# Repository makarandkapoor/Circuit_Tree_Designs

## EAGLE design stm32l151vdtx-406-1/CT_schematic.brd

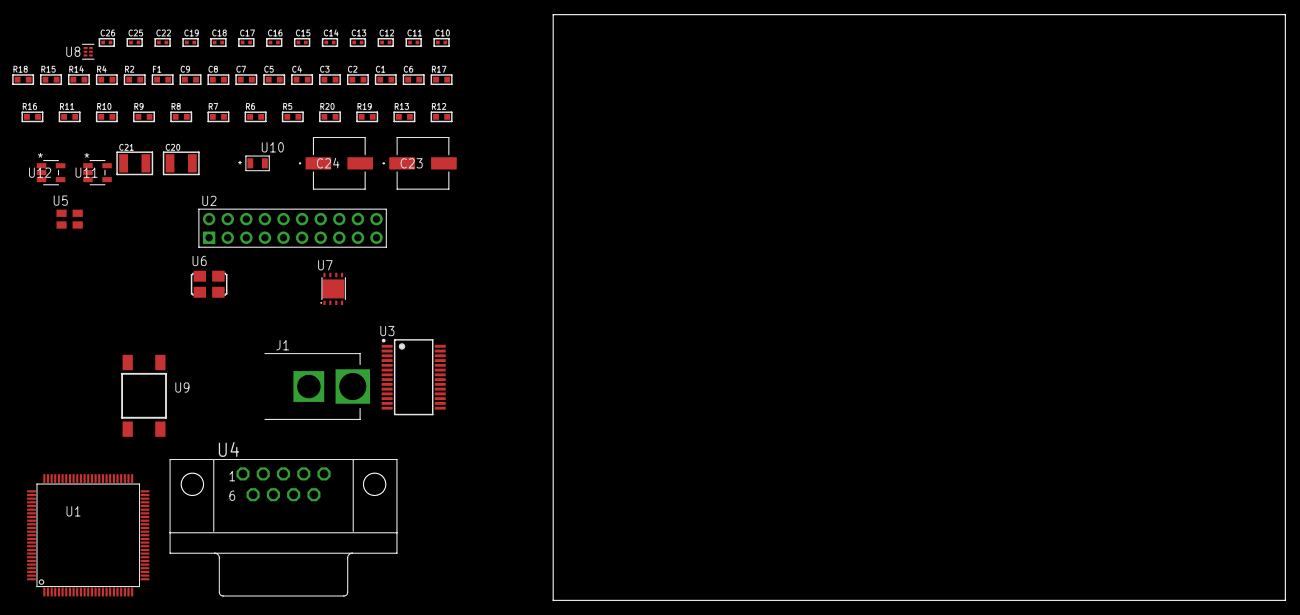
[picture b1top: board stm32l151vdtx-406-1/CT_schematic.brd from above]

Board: 2 copper layers, 100.0 x 80.0 mm, 58 parts (0 on the bottom side), 37 nets, no tracks yet.

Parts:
C1, C2, C3, C4, C5, C7: 1e-07; C0603
C6: 4.7e-06; C0603
C8: 1e-08; C0603
C9: 1e-06; C0603
C10, C11, C12, C13, C14, C15, C16, C22: 1e-07; C0402
C17, C18, C19, C25, C26: 1e-08; C0402
C20, C21: 1e-05; C1210
C23, C24: 0.0001; EXV-9H
F1: 240.0; L0603
J1: PJ-037B; PJ-037B_PACKAGE
R2, R15: 1000.0; R0603
R4: 4700.0; R0603
R5, R6, R7, R8, R9, R10, R11, R16, R17: 10000.0; R0603
R12, R13: 100000.0; R0603
R14: 2231.0; R0603
R18: 9100.0; R0603
R19: 680000.0; R0603
R20: 120000.0; R0603
U1: STM32L151VDT6; LQFP100
U2: TST-110-05-T-D-RA
U3: ST3241EBPR; SSOP-28
U4: 182-009-113R531; 182-009-MALE
U5: ASEK-32.768KHz-ECST; ASEK
U6: ASFL1-25MHZ-NCS; ASFL1
U7: LP3878SDX-ADJ/NOPB; WSON-8
U8: TPS3895ADRYR; SON-6
U9: 4-1437565-2; SW_4-1437565-2
U10: Q65110A2395; LGM67K-G1J2-24-Z
U11, U12: nc7sz125m5x; NC7SZ125M5X

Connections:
CLK_U1_8: U1.8, U5.3
CLK_U1_12: U1.12, U6.3
GND: C1.2, C2.2, C3.2, C4.2, C5.2, C6.2, C7.2, C8.2, C9.2, C10.2, C11.2, C12.2, C15.2, C16.2, C17.2, C18.2, C19.2, C20.2, C21.2, C22.2, C23.2, C24.2, C25.2, C26.2, J1.2, R2.2, R5.2, R11.2, R15.2, R18.2, R20.2, U1.10, U1.19, U1.20, U1.27, U1.49, U1.74, U1.99, U2.4, U2.6, U2.8, U2.10, U2.12, U2.14, U2.16, U2.18, U2.20, U3.23, U3.25, U4.5, U5.2, U6.2, U7.3, U7.PAD, U8.2, U10.C, U11.2, U11.3, U12.1, U12.3
NET_U1_6: C7.1, U1.6
NET_U1_14: R4.1, U1.14, U12.4
NET_U1_22: C8.1, C9.1, F1.1, U1.21, U1.22
NET_U1_94: R5.1, U1.94
NET_U1_98: U9.3, U9.4
NET_U2_19: R11.1, U2.19
NET_U3_1: C14.1, U3.1
NET_U3_2: C14.2, U3.2
NET_U3_3: C16.1, U3.3
NET_U3_22: R12.1, U3.22
NET_U3_24: C13.2, U3.24
NET_U3_27: C15.1, U3.27
NET_U3_28: C13.1, U3.28
NET_U4_2: U3.4, U4.2
NET_U4_3: U3.9, U4.3
NET_U4_7: U3.5, U4.7
NET_U4_8: U3.10, U4.8
NET_U7_1: C19.1, U7.1
NET_U7_6: R14.2, R15.1, U7.6
NET_U7_8: R13.1, U7.8
NET_U8_1: R17.1, R18.1, U8.1
NET_U8_3: R19.2, R20.1, U8.3
NET_U8_4: R16.1, U8.4, U11.4, U12.2
NET_U9_1: R2.1, U9.1, U9.2
PROC_SYS_JTCK_SWCLK: R9.1, U1.76, U2.9
PROC_SYS_JTDI: R7.1, U1.77, U2.5
PROC_SYS_JTDO_TRACESWO: U1.89, U2.13
PROC_SYS_JTMS_SWDIO: R8.1, U1.72, U2.7
PROC_SYS_JTRST: R6.1, U1.90, U2.3
PROC_UART4_RX: U1.79, U3.19
PROC_UART4_TX: U1.78, U3.14
RST_OUT_U2_SRESET_B: R10.1, U2.15, U11.1
VCC_S1_12V4: C20.1, C23.1, C24.1, J1.1, R13.2, U7.4
VCC_TIER1_3V3: C1.1, C2.1, C3.1, C4.1, C5.1, C6.1, C10.1, C11.1, C12.1, C17.1, C18.1, C21.1, C22.1, C25.1, C26.1, F1.2, R4.2, R6.2, R7.2, R8.2, R9.2, R10.2, R12.2, R14.1, R16.2, R17.2, R19.1, U1.11, U1.28, U1.50, U1.75, U1.100, U2.1, U2.2, U3.26, U5.4, U6.4, U7.5, U8.6, U11.5, U12.5

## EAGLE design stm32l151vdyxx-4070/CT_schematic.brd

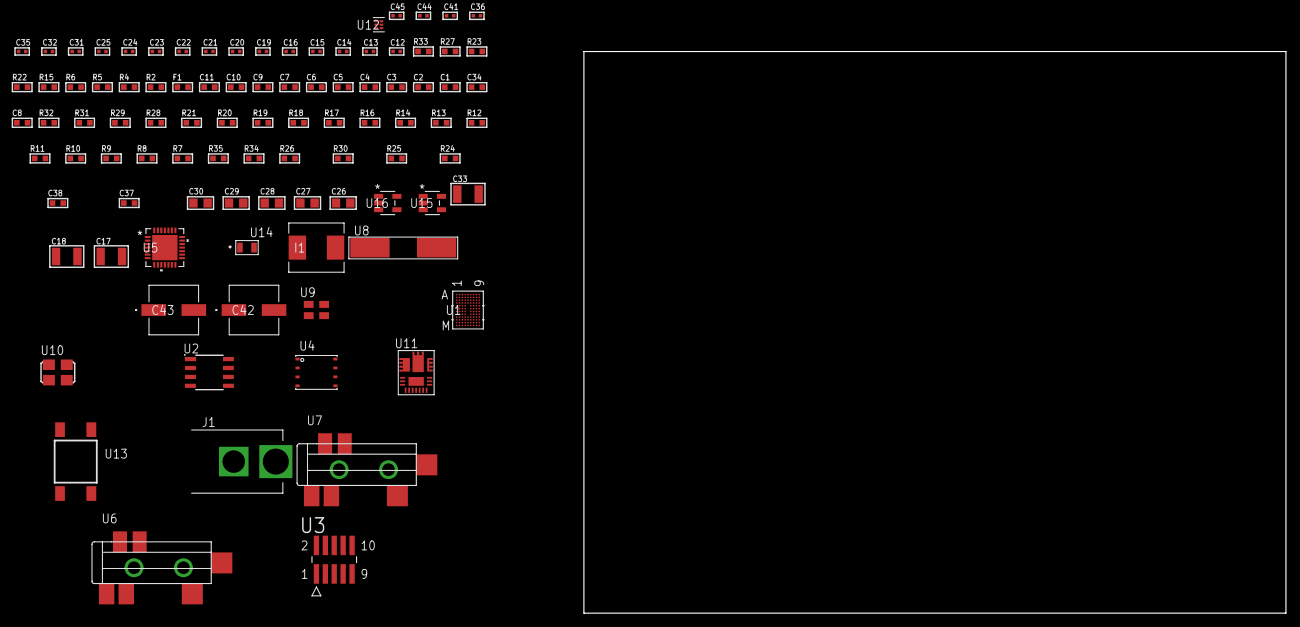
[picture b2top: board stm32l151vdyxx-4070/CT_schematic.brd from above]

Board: 2 copper layers, 100.0 x 80.0 mm, 95 parts (0 on the bottom side), 50 nets, no tracks yet.

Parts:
C1, C2, C3, C4, C5, C6, C7, C9: 1e-07; C0603
C8: 4.7e-06; C0603
C10: 1e-08; C0603
C11: 1e-06; C0603
C12, C13: 1e-11; C0402
C14, C16, C31, C32, C44, C45: 1e-08; C0402
C15, C21, C22, C23, C24, C25, C35, C36, C41: 1e-07; C0402
C17, C18: 2.2e-05; C1210
C19, C20: 1e-09; C0402
C26, C27, C28, C29, C30: 1e-05; C0805
C33: 0.0001; C1210
C34: 2.2e-06; C0603
C37: 8.7488758840791e-09; R0603
C38: 2.9825713241179e-07; R0603
C42, C43: 0.0001; EXV-9H
F1: 240.0; L0603
I1: 6.8e-07; IND25X25CZ
J1: PJ-037B; PJ-037B_PACKAGE
R2: 1000.0; R0603
R4: 4700.0; R0603
R5, R6: 2200.0; R0603
R7, R8, R9, R10, R11, R12, R13, R14, R16, R17, R18, R31, R32: 10000.0; R0603
R15: 5.0; R0603
R19, R20, R21: 47000.0; R0603
R22: 680.0; R0603
R23: 0.1; R0603
R24: 4030.2416170974; R0603
R25: 719.68600305311; R0603
R26: 58.26650887574; R0603
R27: 130.0; R0603
R28: 39000.0; R0603
R29: 49900.0; R0603
R30: 5113.9346405229; R0603
R33: 9100.0; R0603
R34: 680000.0; R0603
R35: 120000.0; R0603
U1: STM32L151VDY6XTR; WLCSP104
U2: AT25320B-SSHL-T; SOIC-8
U3: FTSH-105-01-L-DV-K; SAMTEC_FTSH-105-01-L-DV-K
U4: 24AA256-I/MF; DFN8-S
U5: WM8731CLSEFL; QFN-28
U6, U7: SJ-43515TS-SMT-TR
U8: ABLS-25.000MHZ-B2F-T
U9: ASEK-32.768KHz-ECST; ASEK
U10: ASFL1-12.288MHZ-EC-T; ASFL1
U11: IR3899MTR1PBF
U12: TPS3895ADRYR; SON-6
U13: 4-1437565-2; SW_4-1437565-2
U14: Q65110A2395; LGM67K-G1J2-24-Z
U15, U16: nc7sz125m5x; NC7SZ125M5X

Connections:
CLK_CRYSTAL_U1_F8: C12.1, U1.F8, U8.1
CLK_CRYSTAL_U1_F9: C13.1, U1.F9, U8.2
CLK_U1_D8: U1.D8, U9.3
CLK_U5_1: U5.1, U10.3
GND: C1.2, C2.2, C3.2, C4.2, C5.2, C6.2, C7.2, C8.2, C9.2, C10.2, C11.2, C12.2, C13.2, C14.2, C15.2, C16.2, C20.2, C21.2, C22.2, C23.2, C24.2, C25.2, C26.2, C27.2, C28.2, C29.2, C30.2, C31.2, C32.2, C34.2, C35.2, C36.2, C41.2, C42.2, C43.2, C44.2, C45.2, J1.2, R2.2, R7.2, R14.2, R15.2, R17.2, R18.2, R19.2, R20.2, R21.2, R23.1, R23.2, R25.2, R28.2, R30.2, R33.2, R35.2, U1.A1, U1.C7, U1.D2, U1.E8, U1.H8, U1.J9, U1.K8, U1.L2, U1.M1, U2.4, U3.3, U3.5, U4.4, U5.4, U5.15, U5.19, U5.25, U5.26, U5.29, U6.1, U7.1, U9.2, U10.2, U11.4, U11.11, U11.17, U12.2, U14.C, U15.2, U15.3, U16.1, U16.3
NET_U1_A7: R7.1, U1.A7
NET_U1_B6: R6.1, U1.B6, U4.5
NET_U1_C5: R5.1, U1.C5, U4.6
NET_U1_E7: C9.1, U1.E7
NET_U1_F7: R4.1, U1.F7, U16.4
NET_U1_G6: C10.1, C11.1, F1.1, U1.G6, U1.G7
NET_U1_M8: U13.3, U13.4
NET_U2_3: R8.1, U2.3
NET_U2_7: R10.1, U2.7
NET_U3_9: R15.1, U3.9
NET_U4_1: R16.1, U4.1
NET_U4_2: R17.1, U4.2
NET_U4_3: R18.1, U4.3
NET_U5_20: C25.1, C30.1, U5.20
NET_U6_2: C18.1, R20.1, U6.2
NET_U6_5: C17.1, R19.1, U6.5
NET_U7_5: C19.1, C20.1, R21.1, R22.1, U7.5
NET_U11_1: C37.1, R24.1, R25.1, R26.1, R27.1, U11.1, U11.8
NET_U11_2: C36.1, U11.2
NET_U11_3: C37.2, C38.1, C38.2, U11.3
NET_U11_5: R28.1, U11.5
NET_U11_10: C34.1, U11.10
NET_U11_12: C33.1, I1.1, U11.12
NET_U11_14: C33.2, U11.14
NET_U11_15: R29.1, R30.1, U11.15
NET_U11_ATNET_3: I1.2, R24.2
NET_U11_ATNET_4: C38.2, R26.2
NET_U12_1: R32.1, R33.1, U12.1
NET_U12_3: R34.2, R35.1, U12.3
NET_U12_4: R31.1, U12.4, U15.4, U16.2
NET_U13_1: R2.1, U13.1, U13.2
PROC_I2S2_CK: U1.D4, U5.7
PROC_I2S2_SD: U1.A3, U5.8
PROC_I2S2_WS: U1.A2, U5.9, U5.11
PROC_SPI1_MISO: U1.A5, U2.2
PROC_SPI1_MOSI: U1.A6, U2.5
PROC_SPI1_NSS: R9.1, U1.J7, U2.1
PROC_SPI1_SCK: U1.K5, U2.6
PROC_SYS_JTCK_SWCLK: R14.1, U1.D3, U3.4
PROC_SYS_JTDI: R12.1, U1.B1, U3.8
PROC_SYS_JTDO_TRACESWO: U1.B5, U3.6
PROC_SYS_JTMS_SWDIO: R13.1, U1.E3, U3.2
RST_OUT_U3_JTAG_RST_B: R11.1, U3.10, U15.1
VCC_S1_16V9: C35.1, C42.1, C43.1, J1.1, R29.2, U11.9
VCC_TIER1_3V3: C1.1, C2.1, C3.1, C4.1, C5.1, C6.1, C7.1, C8.1, C14.1, C15.1, C16.1, C21.1, C22.1, C23.1, C24.1, C26.1, C27.1, C28.1, C29.1, C31.1, C32.1, C41.1, C44.1, C45.1, F1.2, I1.2, R4.2, R5.2, R6.2, R8.2, R9.2, R10.2, R11.2, R12.2, R13.2, R16.2, R24.2, R31.2, R32.2, R34.1, U1.A9, U1.B8, U1.C1, U1.E9, U1.K3, U1.L8, U1.M9, U2.8, U3.1, U4.7, U4.8, U5.3, U5.5, U5.12, U5.18, U9.4, U10.4, U12.6, U15.5, U16.5

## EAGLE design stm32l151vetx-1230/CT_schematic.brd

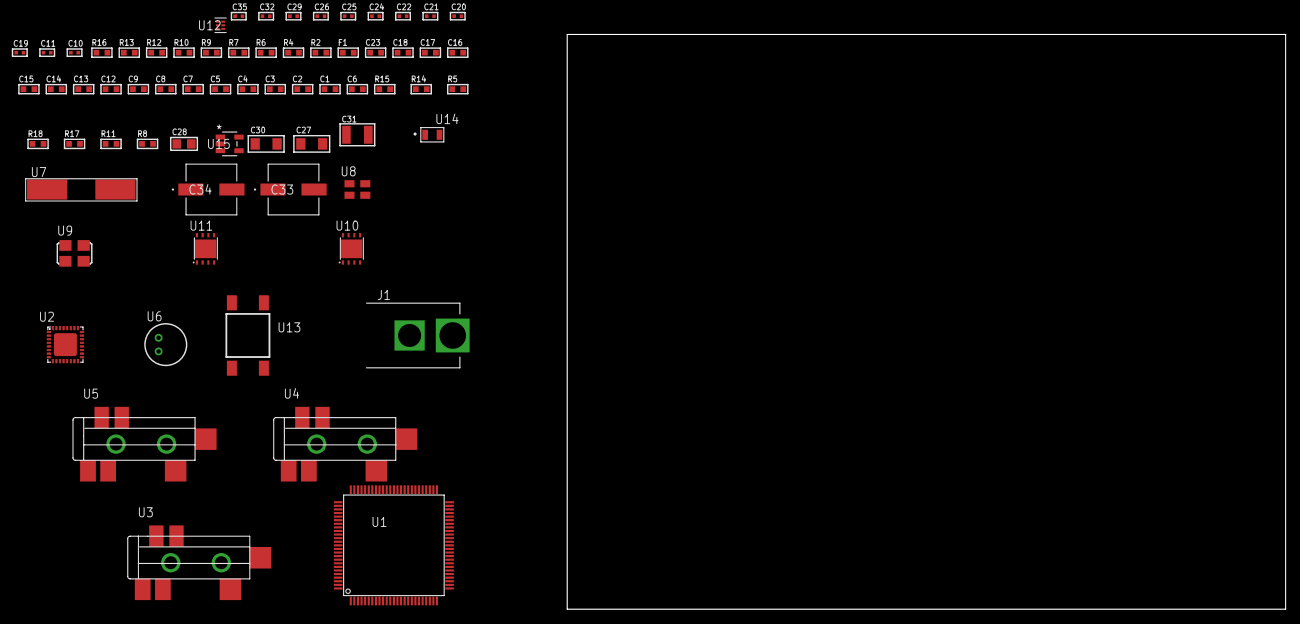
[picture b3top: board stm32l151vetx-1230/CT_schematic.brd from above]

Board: 2 copper layers, 100.0 x 80.0 mm, 68 parts (0 on the bottom side), 39 nets, no tracks yet.

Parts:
C1, C2, C3, C4, C5, C7: 1e-07; C0603
C6: 4.7e-06; C0603
C8: 1e-08; C0603
C9, C12, C13, C14, C15, C16, C17, C18, C23: 1e-06; C0603
C10, C11: 1e-11; C0402
C19, C20, C21, C22, C32: 1e-07; C0402
C24, C25, C26, C29, C35: 1e-08; C0402
C27, C30: 1e-05; C1206
C28: 1e-05; C0805
C31: 1e-05; C1210
C33, C34: 0.0001; EXV-9H
F1: 240.0; L0603
J1: PJ-037B; PJ-037B_PACKAGE
R2, R10, R13: 1000.0; R0603
R4: 4700.0; R0603
R5, R14, R15: 10000.0; R0603
R6, R7: 1270.0; R0603
R8, R11: 100000.0; R0603
R9: 200.0; R0603
R12: 2231.0; R0603
R16: 9100.0; R0603
R17: 680000.0; R0603
R18: 120000.0; R0603
U1: STM32L151VET7; LQFP100
U2: SGTL5000XNAA3; QFN-32
U3, U4, U5: SJ-43515TS-SMT-TR
U6: WM-64PCT; WM-64PC
U7: ABLS-25.000MHZ-B2F-T
U8: ASEK-32.768KHz-ECST; ASEK
U9: ASFL-24.57MHZ-NCS; ASFL1
U10, U11: LP3878SDX-ADJ/NOPB; WSON-8
U12: TPS3895ADRYR; SON-6
U13: 4-1437565-2; SW_4-1437565-2
U14: Q65110A2395; LGM67K-G1J2-24-Z
U15: nc7sz125m5x; NC7SZ125M5X

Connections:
CLK_CRYSTAL_U1_12: C10.1, U1.12, U7.1
CLK_CRYSTAL_U1_13: C11.1, U1.13, U7.2
CLK_U1_8: U1.8, U8.3
CLK_U2_21: U2.21, U9.3
GND: C1.2, C2.2, C3.2, C4.2, C5.2, C6.2, C7.2, C8.2, C9.2, C10.2, C11.2, C19.2, C20.2, C21.2, C22.2, C23.2, C24.2, C25.2, C26.2, C27.2, C28.2, C29.2, C30.2, C31.2, C32.2, C33.2, C34.2, C35.2, J1.2, R2.2, R5.2, R7.2, R10.2, R13.2, R16.2, R18.2, U1.10, U1.19, U1.20, U1.27, U1.49, U1.74, U1.99, U2.1, U2.3, U2.7, U2.EXP, U4.1, U5.1, U6.2, U8.2, U9.2, U10.3, U10.PAD, U11.3, U11.PAD, U12.2, U14.C, U15.1, U15.3
NET_U1_6: C7.1, U1.6
NET_U1_14: R4.1, U1.14, U15.4
NET_U1_22: C8.1, C9.1, F1.1, U1.21, U1.22
NET_U1_94: R5.1, U1.94
NET_U1_98: U13.3, U13.4
NET_U2_10: C22.1, U2.10
NET_U2_29: R6.1, U2.29
NET_U2_31: R7.1, U2.31
NET_U3_1: U2.4, U3.1
NET_U3_2: U2.2, U3.2
NET_U3_5: U2.6, U3.5
NET_U4_2: C13.1, U4.2
NET_U4_5: C12.1, U4.5
NET_U5_2: C15.1, C16.1, U5.2
NET_U5_5: C14.1, U5.5
NET_U5_13: C15.2, C16.2
NET_U6_1: C17.1, C18.1, C23.1, U2.16, U6.1
NET_U6_15: C17.2, C18.2
NET_U10_1: C26.1, U10.1
NET_U10_6: R9.2, R10.1, U10.6
NET_U10_8: R8.1, U10.8
NET_U11_1: C29.1, U11.1
NET_U11_6: R12.2, R13.1, U11.6
NET_U11_8: R11.1, U11.8
NET_U12_1: R15.1, R16.1, U12.1
NET_U12_3: R17.2, R18.1, U12.3
NET_U12_4: R14.1, U12.4, U15.2
NET_U13_1: R2.1, U13.1, U13.2
PROC_I2S2_CK: U1.52, U2.24
PROC_I2S2_SD: U1.54, U2.26
PROC_I2S2_WS: U1.51, U2.23
VCC_S1_6V1: C27.1, C30.1, C33.1, C34.1, J1.1, R8.2, R11.2, U10.4, U11.4
VCC_TIER1_1V2: C19.1, C28.1, R9.1, U2.30, U10.5
VCC_TIER1_3V3: C1.1, C2.1, C3.1, C4.1, C5.1, C6.1, C20.1, C21.1, C24.1, C25.1, C31.1, C32.1, C35.1, F1.2, R4.2, R6.2, R12.1, R14.2, R15.2, R17.1, U1.11, U1.28, U1.50, U1.75, U1.100, U2.5, U2.20, U8.4, U9.4, U11.5, U12.6, U15.5

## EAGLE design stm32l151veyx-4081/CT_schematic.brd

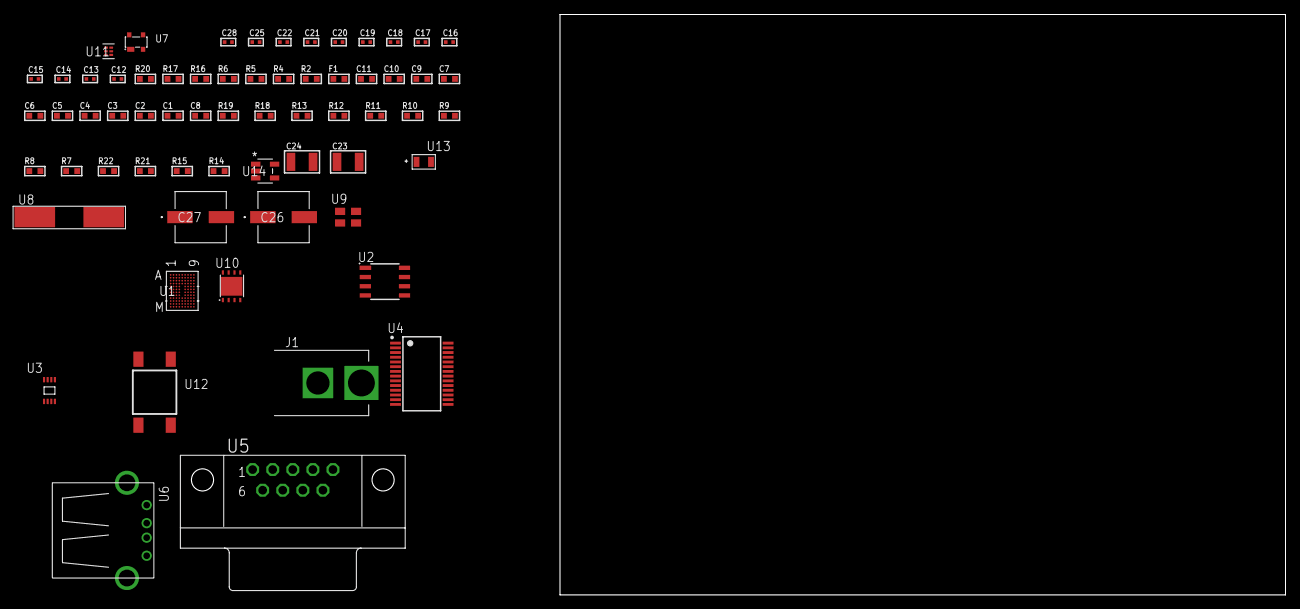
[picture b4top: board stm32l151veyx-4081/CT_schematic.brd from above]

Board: 2 copper layers, 100.0 x 80.0 mm, 64 parts (0 on the bottom side), 45 nets, no tracks yet.

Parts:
C1, C2, C3, C4, C5, C6, C7, C9: 1e-07; C0603
C8: 4.7e-06; C0603
C10: 1e-08; C0603
C11: 1e-06; C0603
C12, C13: 1e-11; C0402
C14, C15, C21, C22, C28: 1e-08; C0402
C16, C17, C18, C19, C20, C25: 1e-07; C0402
C23, C24: 1e-05; C1210
C26, C27: 0.0001; EXV-9H
F1: 240.0; L0603
J1: PJ-037B; PJ-037B_PACKAGE
R2, R17: 1000.0; R0603
R4: 4700.0; R0603
R5, R6: 2200.0; R0603
R7, R8, R9, R10, R11, R12, R13, R18, R19: 10000.0; R0603
R14, R15: 100000.0; R0603
R16: 2231.0; R0603
R20: 9100.0; R0603
R21: 680000.0; R0603
R22: 120000.0; R0603
U1: STM32L151VEY6TR; WLCSP104
U2: AT25020B-SSHL-T; SOIC-8
U3: 24AA64T-I/MNY; TDFN-8/6MM
U4: ST3241EBPR; SSOP-28
U5: 182-009-113R531; 182-009-MALE
U6: 61400416021; USB-A-H
U7: prtr5v0u2ax; SOT143B
U8: ABLS-25.000MHZ-B2F-T
U9: ASEK-32.768KHz-ECST; ASEK
U10: LP3878SDX-ADJ/NOPB; WSON-8
U11: TPS3895ADRYR; SON-6
U12: 4-1437565-2; SW_4-1437565-2
U13: Q65110A2395; LGM67K-G1J2-24-Z
U14: nc7sz125m5x; NC7SZ125M5X

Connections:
CLK_CRYSTAL_U1_F8: C12.1, U1.F8, U8.1
CLK_CRYSTAL_U1_F9: C13.1, U1.F9, U8.2
CLK_U1_D8: U1.D8, U9.3
GND: C1.2, C2.2, C3.2, C4.2, C5.2, C6.2, C7.2, C8.2, C9.2, C10.2, C11.2, C12.2, C13.2, C14.2, C15.2, C16.2, C19.2, C20.2, C21.2, C22.2, C23.2, C24.2, C25.2, C26.2, C27.2, C28.2, J1.2, R2.2, R7.2, R17.2, R20.2, R22.2, U1.A1, U1.C7, U1.D2, U1.E8, U1.H8, U1.J9, U1.K8, U1.L2, U1.M1, U2.4, U3.4, U4.23, U4.25, U5.5, U6.4, U6.5, U6.6, U7.1, U9.2, U10.3, U10.PAD, U11.2, U13.C, U14.1, U14.3
NET_U1_A7: R7.1, U1.A7
NET_U1_B6: R6.1, U1.B6, U3.5
NET_U1_C5: R5.1, U1.C5, U3.6
NET_U1_E7: C9.1, U1.E7
NET_U1_F7: R4.1, U1.F7, U14.4
NET_U1_G6: C10.1, C11.1, F1.1, U1.G6, U1.G7
NET_U1_M8: U12.3, U12.4
NET_U2_3: R8.1, U2.3
NET_U2_7: R10.1, U2.7
NET_U3_1: R11.1, U3.1
NET_U3_2: R12.1, U3.2
NET_U3_3: R13.1, U3.3
NET_U4_1: C18.1, U4.1
NET_U4_2: C18.2, U4.2
NET_U4_3: C20.1, U4.3
NET_U4_22: R14.1, U4.22
NET_U4_24: C17.2, U4.24
NET_U4_27: C19.1, U4.27
NET_U4_28: C17.1, U4.28
NET_U5_2: U4.4, U5.2
NET_U5_3: U4.9, U5.3
NET_U5_7: U4.5, U5.7
NET_U5_8: U4.10, U5.8
NET_U7_4: U6.1, U7.4
NET_U10_1: C22.1, U10.1
NET_U10_6: R16.2, R17.1, U10.6
NET_U10_8: R15.1, U10.8
NET_U11_1: R19.1, R20.1, U11.1
NET_U11_3: R21.2, R22.1, U11.3
NET_U11_4: R18.1, U11.4, U14.2
NET_U12_1: R2.1, U12.1, U12.2
PROC_SPI1_MISO: U1.A5, U2.2
PROC_SPI1_MOSI: U1.A6, U2.5
PROC_SPI1_NSS: R9.1, U1.B1, U2.1
PROC_SPI1_SCK: U1.B5, U2.6
PROC_UART4_RX: U1.C2, U4.19
PROC_UART4_TX: U1.E4, U4.14
PROC_USB_DM: U1.E1, U6.2, U7.3
PROC_USB_DP: U1.E2, U6.3, U7.2
VCC_S1_15V3: C23.1, C26.1, C27.1, J1.1, R15.2, U10.4
VCC_TIER1_3V3: C1.1, C2.1, C3.1, C4.1, C5.1, C6.1, C7.1, C8.1, C14.1, C15.1, C16.1, C21.1, C24.1, C25.1, C28.1, F1.2, R4.2, R5.2, R6.2, R8.2, R9.2, R10.2, R11.2, R12.2, R13.2, R14.2, R16.1, R18.2, R19.2, R21.1, U1.A9, U1.B8, U1.C1, U1.E9, U1.K3, U1.L8, U1.M9, U2.8, U3.7, U3.8, U4.26, U9.4, U10.5, U11.6, U14.5

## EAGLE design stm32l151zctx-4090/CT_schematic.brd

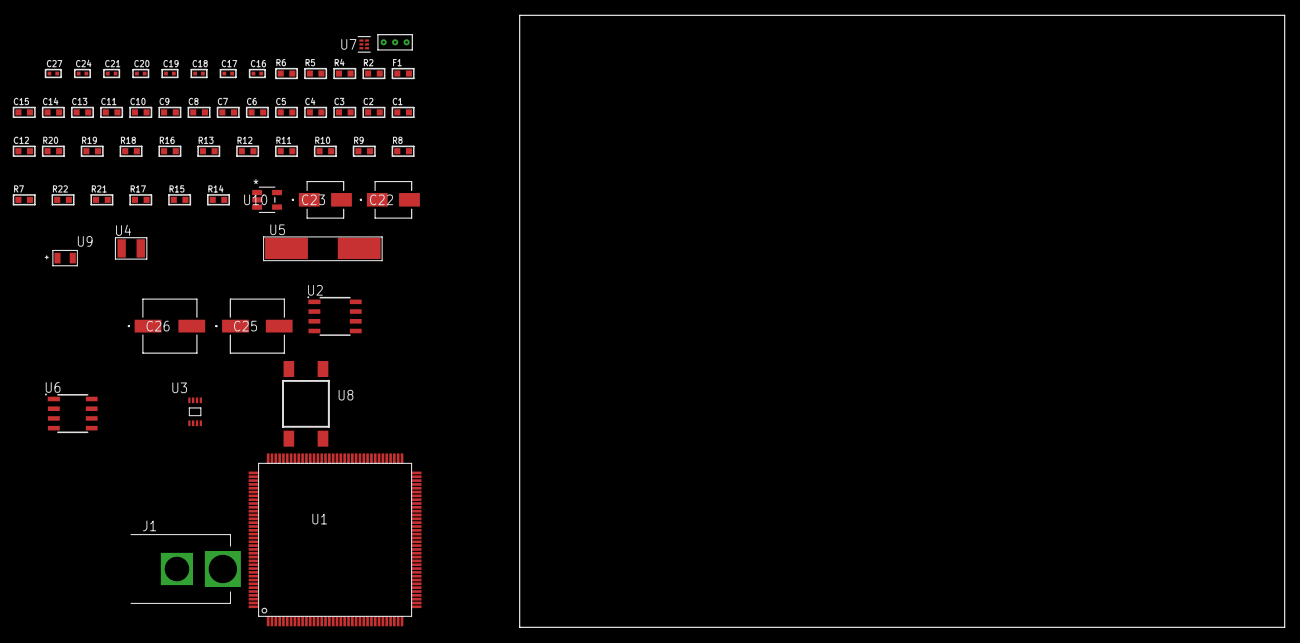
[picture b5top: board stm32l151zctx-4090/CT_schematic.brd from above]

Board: 2 copper layers, 100.0 x 80.0 mm, 60 parts (0 on the bottom side), 32 nets, no tracks yet.

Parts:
C1, C2, C3, C4, C5, C6, C7, C8, C9, C10, C11, C13: 1e-07; C0603
C12: 4.7e-06; C0603
C14: 1e-08; C0603
C15: 1e-06; C0603
C16, C17, C18, C19: 1e-11; C0402
C20, C21, C27: 1e-08; C0402
C22: 1e-06; EXV-9B
C23: 2.2e-06; EXV-9B
C24: 1e-07; C0402
C25, C26: 0.0001; EXV-9H
F1: 240.0; L0603
J1: PJ-037B; PJ-037B_PACKAGE
R2: 1000.0; R0603
R4: 4700.0; R0603
R5, R6: 2200.0; R0603
R7, R8, R9, R10, R11, R12, R13, R18, R19: 10000.0; R0603
R14, R15, R17: 100000.0; R0603
R16: 47000.0; R0603
R20: 82000.0; R0603
R21: 300000.0; R0603
R22: 120000.0; R0603
U1: STM32L151ZCT6; LQFP144
U2: AT25320B-SSHL-T; SOIC-8
U3: 24AA64T-I/MNY; TDFN-8/6MM
U4: ABS07-32.768KHZ-7-T
U5: ABLS-25.000MHZ-B2F-T
U6: LP2954AIMX/NOPB; LP2954
U7: TPS3895ADRYR; SON-6
U8: 4-1437565-2; SW_4-1437565-2
U9: Q65110A2395; LGM67K-G1J2-24-Z
U10: nc7sz125m5x; NC7SZ125M5X
U11: Dummy; DUMMY_PACKAGE_122

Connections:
CLK_CRYSTAL_U1_8: C16.1, U1.8, U4.1
CLK_CRYSTAL_U1_9: C17.1, U1.9, U4.2
CLK_CRYSTAL_U1_23: C18.1, U1.23, U5.1
CLK_CRYSTAL_U1_24: C19.1, U1.24, U5.2
GND: C1.2, C2.2, C3.2, C4.2, C5.2, C6.2, C7.2, C8.2, C9.2, C10.2, C11.2, C12.2, C13.2, C14.2, C15.2, C16.2, C17.2, C18.2, C19.2, C20.2, C21.2, C22.2, C23.2, C24.2, C25.2, C26.2, C27.2, J1.2, R2.2, R7.2, R17.2, R20.2, R22.2, U1.16, U1.30, U1.31, U1.38, U1.51, U1.61, U1.71, U1.83, U1.94, U1.107, U1.120, U1.130, U1.143, U2.4, U3.4, U6.4, U7.2, U9.C, U10.1, U10.3, U11.1
NET_U1_6: C13.1, U1.6
NET_U1_25: R4.1, U1.25, U10.4
NET_U1_33: C14.1, C15.1, F1.1, U1.32, U1.33
NET_U1_136: R5.1, U1.136, U3.6
NET_U1_137: R6.1, U1.137, U3.5
NET_U1_138: R7.1, U1.138
NET_U1_142: U8.3, U8.4
NET_U2_3: R8.1, U2.3
NET_U2_7: R10.1, U2.7
NET_U3_1: R11.1, U3.1
NET_U3_2: R12.1, U3.2
NET_U3_3: R13.1, U3.3
NET_U6_3: R15.1, U6.3
NET_U6_5: R14.1, U6.5
NET_U6_7: R16.2, R17.1, U6.7
NET_U7_1: R19.1, R20.1, U7.1
NET_U7_3: R21.2, R22.1, U7.3
NET_U7_4: R18.1, U7.4, U10.2
NET_U8_1: R2.1, U8.1, U8.2
PROC_SPI1_MISO: U1.42, U2.2
PROC_SPI1_MOSI: U1.43, U2.5
PROC_SPI1_NSS: R9.1, U1.40, U2.1
PROC_SPI1_SCK: U1.41, U2.6
PROC_TIM2_CH1: U1.34, U11.3
PROC_TIM2_CH3: U1.36, U11.2
VCC_S1_14V9: C22.1, C25.1, C26.1, J1.1, R15.2, U6.8
VCC_TIER1_1V8: C1.1, C2.1, C3.1, C4.1, C5.1, C6.1, C7.1, C8.1, C9.1, C10.1, C11.1, C12.1, C20.1, C21.1, C23.1, C24.1, C27.1, F1.2, R4.2, R5.2, R6.2, R8.2, R9.2, R10.2, R11.2, R12.2, R13.2, R14.2, R16.1, R18.2, R19.2, R21.1, U1.17, U1.39, U1.52, U1.62, U1.72, U1.84, U1.95, U1.108, U1.121, U1.131, U1.144, U2.8, U3.7, U3.8, U6.1, U7.6, U10.5

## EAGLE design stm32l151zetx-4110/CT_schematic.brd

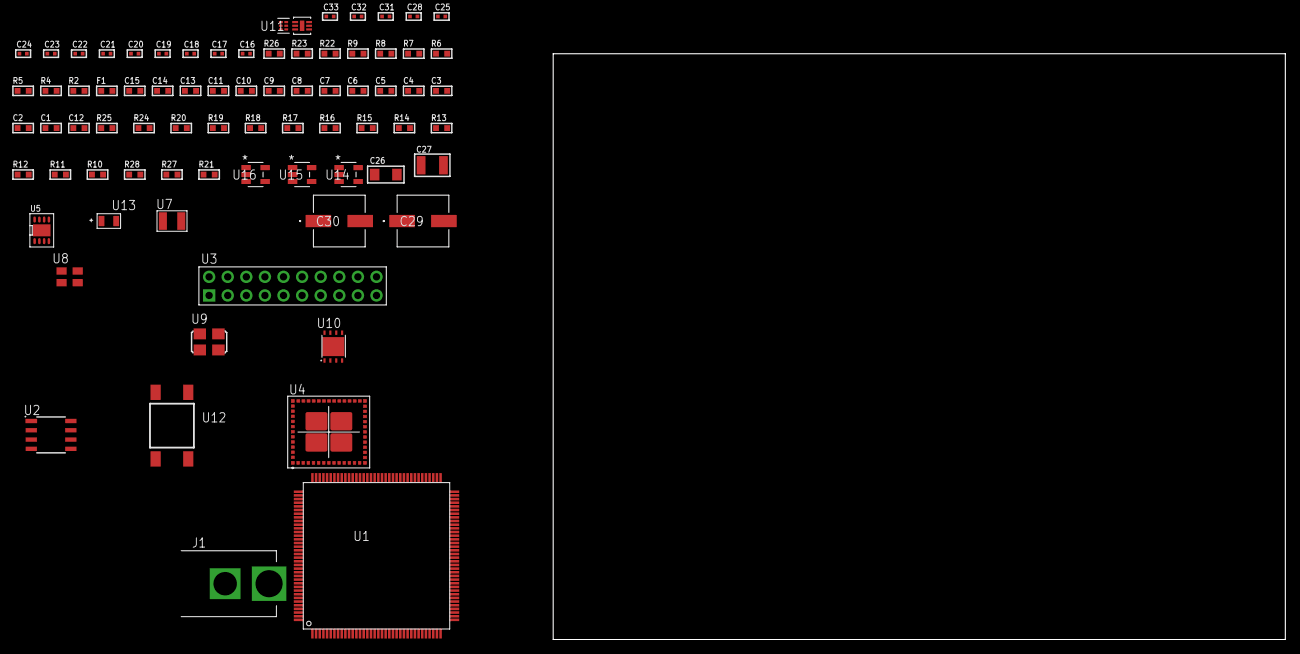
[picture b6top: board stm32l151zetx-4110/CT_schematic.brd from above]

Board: 2 copper layers, 100.0 x 80.0 mm, 77 parts (0 on the bottom side), 40 nets, no tracks yet.

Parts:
C1, C2, C3, C4, C5, C6, C7, C8, C9, C10, C11, C13: 1e-07; C0603
C12: 4.7e-06; C0603
C14: 1e-08; C0603
C15: 1e-06; C0603
C16, C23, C24, C25, C31, C32, C33: 1e-08; C0402
C17, C18, C19, C20, C21, C22, C28: 1e-07; C0402
C26: 1e-05; C1206
C27: 1e-05; C1210
C29, C30: 0.0001; EXV-9H
F1: 240.0; L0603
J1: PJ-037B; PJ-037B_PACKAGE
R2, R23: 1000.0; R0603
R4, R5: 4700.0; R0603
R6, R7, R8, R9: 2200.0; R0603
R10, R11, R12, R13, R14, R15, R16, R17, R18, R19, R20, R24, R25: 10000.0; R0603
R21: 100000.0; R0603
R22: 2231.0; R0603
R26: 9100.0; R0603
R27: 680000.0; R0603
R28: 120000.0; R0603
U1: STM32L151ZET6; LQFP144
U2: AT25128B-SSHL-T; SOIC-8
U3: TST-110-05-T-D-RA
U4: MBH7BLZ02-109004
U5: PCF85063TP/1Z; SON-8
U6: Si7051-A20-IM; DFN-6
U7: ABS07-32.768KHZ-7-T
U8: ASEK-32.768KHz-ECST; ASEK
U9: ASFL1-25MHZ-NCS; ASFL1
U10: LP3878SDX-ADJ/NOPB; WSON-8
U11: TPS3895ADRYR; SON-6
U12: 4-1437565-2; SW_4-1437565-2
U13: Q65110A2395; LGM67K-G1J2-24-Z
U14, U15, U16: nc7sz125m5x; NC7SZ125M5X

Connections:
CLK_CRYSTAL_U5_1: U5.1, U7.1
CLK_CRYSTAL_U5_2: U5.2, U7.2
CLK_U1_8: U1.8, U8.3
CLK_U1_23: U1.23, U9.3
GND: C1.2, C2.2, C3.2, C4.2, C5.2, C6.2, C7.2, C8.2, C9.2, C10.2, C11.2, C12.2, C13.2, C14.2, C15.2, C16.2, C17.2, C18.2, C19.2, C20.2, C21.2, C22.2, C23.2, C24.2, C25.2, C26.2, C27.2, C28.2, C29.2, C30.2, C31.2, C32.2, C33.2, J1.2, R2.2, R10.2, R19.2, R23.2, R26.2, R28.2, U1.16, U1.30, U1.31, U1.38, U1.51, U1.61, U1.71, U1.83, U1.94, U1.107, U1.120, U1.130, U1.143, U2.4, U3.4, U3.6, U3.8, U3.10, U3.12, U3.14, U3.16, U3.18, U3.20, U4.1, U4.3, U4.15, U4.27, U4.29, U4.41, U4.42, U4.43, U4.44, U4.45, U4.46, U4.47, U4.48, U4.49, U4.50, U4.52, U4.53, U4.54, U4.55, U4.56, U5.4, U5.PAD, U6.2, U6.7, U8.2, U9.2, U10.3, U10.PAD, U11.2, U13.C, U14.2, U14.3, U15.1, U15.3, U16.1, U16.3
NET_U1_6: C13.1, U1.6
NET_U1_25: R5.1, U1.25, U16.4
NET_U1_33: C14.1, C15.1, F1.1, U1.32, U1.33
NET_U1_69: R8.1, U1.69, U6.6
NET_U1_70: R9.1, U1.70, U6.1
NET_U1_136: R6.1, U1.136, U5.6
NET_U1_137: R7.1, U1.137, U5.5
NET_U1_138: R10.1, U1.138
NET_U1_142: U12.3, U12.4
NET_U2_3: R11.1, U2.3
NET_U2_7: R13.1, U2.7
NET_U3_19: R19.1, U3.19
NET_U4_39: R4.1, U4.39, U15.4
NET_U5_3: R20.1, U5.3
NET_U10_1: C25.1, U10.1
NET_U10_6: R22.2, R23.1, U10.6
NET_U10_8: R21.1, U10.8
NET_U11_1: R25.1, R26.1, U11.1
NET_U11_3: R27.2, R28.1, U11.3
NET_U11_4: R24.1, U11.4, U14.4, U15.2, U16.2
NET_U12_1: R2.1, U12.1, U12.2
PROC_SPI1_MISO: U1.42, U2.2
PROC_SPI1_MOSI: U1.43, U2.5
PROC_SPI1_NSS: R12.1, U1.40, U2.1
PROC_SPI1_SCK: U1.41, U2.6
PROC_SYS_JTCK_SWCLK: R17.1, U1.109, U3.9
PROC_SYS_JTDI: R15.1, U1.110, U3.5
PROC_SYS_JTDO_TRACESWO: U1.133, U3.13
PROC_SYS_JTMS_SWDIO: R16.1, U1.105, U3.7
PROC_SYS_JTRST: R14.1, U1.134, U3.3
PROC_UART4_RX: U1.112, U4.25
PROC_UART4_TX: U1.111, U4.23
RST_OUT_U3_SRESET_B: R18.1, U3.15, U14.1
VCC_S1_8V6: C26.1, C29.1, C30.1, J1.1, R21.2, U10.4
VCC_TIER1_3V3: C1.1, C2.1, C3.1, C4.1, C5.1, C6.1, C7.1, C8.1, C9.1, C10.1, C11.1, C12.1, C16.1, C17.1, C18.1, C19.1, C20.1, C21.1, C22.1, C23.1, C24.1, C27.1, C28.1, C31.1, C32.1, C33.1, F1.2, R4.2, R5.2, R6.2, R7.2, R8.2, R9.2, R11.2, R12.2, R13.2, R14.2, R15.2, R16.2, R17.2, R18.2, R20.2, R22.1, R24.2, R25.2, R27.1, U1.17, U1.39, U1.52, U1.62, U1.72, U1.84, U1.95, U1.108, U1.121, U1.131, U1.144, U2.8, U3.1, U3.2, U4.28, U5.8, U6.5, U8.4, U9.4, U10.5, U11.6, U14.5, U15.5, U16.5

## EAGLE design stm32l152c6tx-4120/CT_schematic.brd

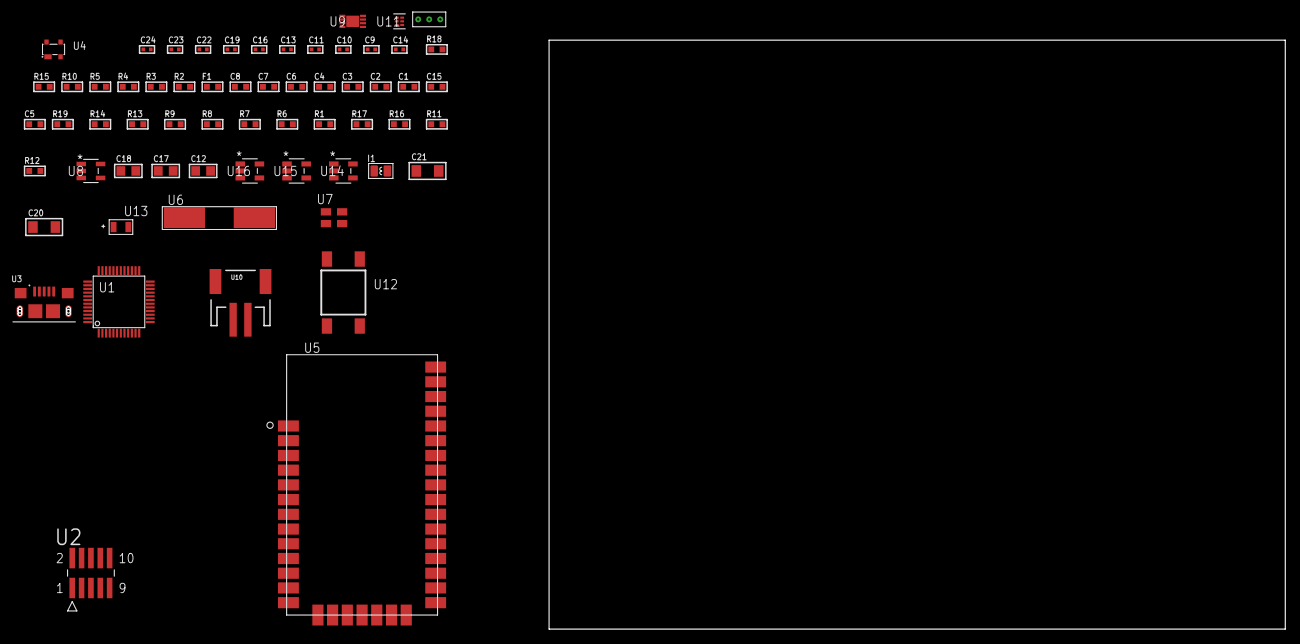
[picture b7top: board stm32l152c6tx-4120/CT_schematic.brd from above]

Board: 2 copper layers, 172.1 x 80.0 mm, 62 parts (0 on the bottom side), 36 nets, no tracks yet.

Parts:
C1, C2, C3, C4, C6: 1e-07; C0603
C5: 4.7e-06; C0603
C7: 1e-08; C0603
C8: 1e-06; C0603
C9, C10: 1e-11; C0402
C11, C13, C19: 1e-07; C0402
C12, C17, C18: 1e-05; C0805
C14: 4.7e-11; C0402
C15: 8.2e-12; C0603
C16, C22, C23, C24: 1e-08; C0402
C20, C21: 1e-05; C1206
F1: 240.0; L0603
I1: 3.3e-06; L0806
R1, R6, R7, R8, R9, R13, R14, R19: 10000.0; R0603
R2: 1000.0; R0603
R3: 1600.5; R0603
R4, R5: 4700.0; R0603
R10: 5.0; R0603
R11: 220000.0; R0603
R12: 1000000.0; R0603
R15: 9100.0; R0603
R16: 680000.0; R0603
R17: 120000.0; R0603
R18: 2000.0; R0603
U1: STM32L152C6T6; LQFP48
U2: FTSH-105-01-L-DV-K; SAMTEC_FTSH-105-01-L-DV-K
U3: 10118193-0001LF; FCI_10118193-0001LF
U4: prtr5v0u2ax; SOT143B
U5: XB24CZ7UIS-004
U6: ABLS-25.000MHZ-B2F-T
U7: ASEK-32.768KHz-ECST; ASEK
U8: ltc3406es5; TSOT-23-5
U9: MCP73831T-2ACI/MC; DFN8_2X3MC
U10: S2B-PH-SM4-TB(LF)(SN); JST-2-SMD
U11: TPS3895ADRYR; SON-6
U12: 4-1437565-2; SW_4-1437565-2
U13: Q65110A2395; LGM67K-G1J2-24-Z
U14, U15, U16: nc7sz125m5x; NC7SZ125M5X
U17: Dummy; DUMMY_PACKAGE_129

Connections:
CLK_CRYSTAL_U1_5: C9.1, U1.5, U6.1
CLK_CRYSTAL_U1_6: C10.1, U1.6, U6.2
CLK_U1_3: U1.3, U7.3
GND: C1.2, C2.2, C3.2, C4.2, C5.2, C6.2, C7.2, C8.2, C9.2, C10.2, C11.2, C12.2, C13.2, C14.2, C15.2, C16.2, C17.2, C18.1, C18.2, C19.2, C20.2, C21.2, C22.2, C23.2, C24.2, R2.2, R6.2, R10.2, R11.2, R15.2, R17.2, R18.2, U1.8, U1.23, U1.35, U1.47, U2.3, U2.5, U3.5, U3.6, U3.7, U3.8, U3.9, U4.1, U5.1, U5.11, U5.13, U5.22, U5.35, U7.2, U8.2, U9.6, U9.9, U10.2, U11.2, U13.C, U14.2, U14.3, U15.1, U15.3, U16.1, U16.3, U17.1
INPUT_USBPOWER_5V: C20.1, R19.2, U3.1, U4.4, U9.1, U9.2
NET_U1_1: C6.1, U1.1
NET_U1_7: R5.1, U1.7, U16.4
NET_U1_9: C7.1, C8.1, F1.1, U1.9
NET_U1_44: R6.1, U1.44
NET_U1_45: R3.1, U1.45, U13.A
NET_U1_46: R1.1, U1.46, U12.3, U12.4
NET_U2_9: R10.1, U2.9
NET_U5_6: R4.1, U5.6, U15.4
NET_U8_3: I1.1, U8.3
NET_U8_5: R11.1, R12.1, U8.5
NET_U8_ATNET_3: I1.2, R12.2
NET_U9_5: R19.1, U9.5
NET_U9_8: R18.1, U9.8
NET_U11_1: R14.1, R15.1, U11.1
NET_U11_3: R16.2, R17.1, U11.3
NET_U11_4: R13.1, U11.4, U14.4, U15.2, U16.2
NET_U12_1: R2.1, U12.1, U12.2
PROC_PC13_WKUP2: U1.2, U17.2
PROC_PC15_OSC32_OUT: U1.4, U17.3
PROC_SPI1_MISO: U1.16, U5.17
PROC_SPI1_MOSI: U1.17, U5.16
PROC_SPI1_NSS: U1.14, U5.15
PROC_SPI1_SCK: U1.15, U5.14
PROC_SYS_JTCK_SWCLK: R8.1, U1.37, U2.4
PROC_SYS_JTDO_TRACESWO: U1.39, U2.6
PROC_SYS_JTMS_SWDIO: R9.1, U1.34, U2.2
PROC_USB_DM: U1.32, U3.2, U4.3
PROC_USB_DP: U1.33, U3.3, U4.2
RST_OUT_U2_JTAG_RST_B: R7.1, U2.10, U14.1
VCC_S1_3V7: C17.1, C21.1, U8.4, U9.3, U9.4, U10.1
VCC_TIER1_3V3: C1.1, C2.1, C3.1, C4.1, C5.1, C11.1, C12.1, C13.1, C14.1, C15.1, C16.1, C18.2, C19.1, C22.1, C23.1, C24.1, F1.2, I1.2, R1.2, R3.2, R4.2, R5.2, R7.2, R8.2, R9.2, R12.2, R13.2, R14.2, R16.1, U1.24, U1.36, U1.48, U2.1, U5.2, U5.27, U7.4, U11.6, U14.5, U15.5, U16.5

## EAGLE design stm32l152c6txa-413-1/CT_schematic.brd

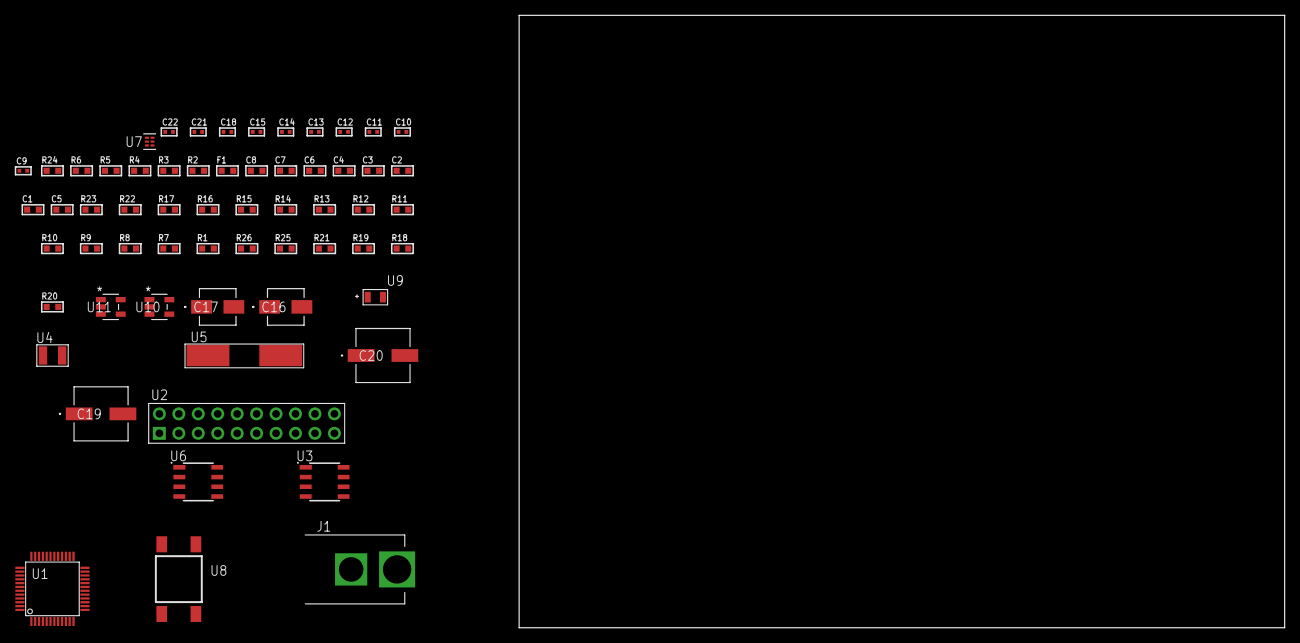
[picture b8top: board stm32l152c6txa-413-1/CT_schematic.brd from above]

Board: 2 copper layers, 100.0 x 80.0 mm, 61 parts (0 on the bottom side), 33 nets, no tracks yet.

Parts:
C1, C2, C3, C4, C6: 1e-07; C0603
C5: 4.7e-06; C0603
C7: 1e-08; C0603
C8: 1e-06; C0603
C9, C10, C11, C12: 1e-11; C0402
C13, C14, C18: 1e-07; C0402
C15, C21, C22: 1e-08; C0402
C16: 1e-06; EXV-9B
C17: 2.2e-06; EXV-9B
C19, C20: 0.0001; EXV-9H
F1: 240.0; L0603
J1: PJ-037B; PJ-037B_PACKAGE
R1, R7, R8, R9, R10, R11, R12, R13, R14, R15, R16, R17, R22, R23: 10000.0; R0603
R2: 1000.0; R0603
R3: 1600.5; R0603
R4: 4700.0; R0603
R5, R6: 2200.0; R0603
R18, R19, R21: 100000.0; R0603
R20: 164658.62; R0603
R24: 9100.0; R0603
R25: 680000.0; R0603
R26: 120000.0; R0603
U1: STM32L152C6T6A; LQFP48
U2: TST-110-05-T-D-RA
U3: AT24C02D-SSHM-T; AT24C02D
U4: ABS07-32.768KHZ-7-T
U5: ABLS-25.000MHZ-B2F-T
U6: LP2954AIMX/NOPB; LP2954
U7: TPS3895ADRYR; SON-6
U8: 4-1437565-2; SW_4-1437565-2
U9: Q65110A2395; LGM67K-G1J2-24-Z
U10, U11: nc7sz125m5x; NC7SZ125M5X

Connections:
CLK_CRYSTAL_U1_3: C9.1, U1.3, U4.1
CLK_CRYSTAL_U1_4: C10.1, U1.4, U4.2
CLK_CRYSTAL_U1_5: C11.1, U1.5, U5.1
CLK_CRYSTAL_U1_6: C12.1, U1.6, U5.2
GND: C1.2, C2.2, C3.2, C4.2, C5.2, C6.2, C7.2, C8.2, C9.2, C10.2, C11.2, C12.2, C13.2, C14.2, C15.2, C16.2, C17.2, C18.2, C19.2, C20.2, C21.2, C22.2, J1.2, R2.2, R7.2, R13.2, R14.2, R16.2, R17.2, R21.2, R24.2, R26.2, U1.8, U1.23, U1.35, U1.47, U2.4, U2.6, U2.8, U2.10, U2.12, U2.14, U2.16, U2.18, U2.20, U3.4, U6.4, U7.2, U9.C, U10.2, U10.3, U11.1, U11.3
NET_U1_1: C6.1, U1.1
NET_U1_7: R4.1, U1.7, U11.4
NET_U1_9: C7.1, C8.1, F1.1, U1.9
NET_U1_42: R5.1, U1.42, U3.6
NET_U1_43: R6.1, U1.43, U3.5
NET_U1_44: R7.1, U1.44
NET_U1_45: R3.1, U1.45, U9.A
NET_U1_46: R1.1, U1.46, U8.3, U8.4
NET_U2_19: R13.1, U2.19
NET_U3_1: R15.1, U3.1
NET_U3_2: R16.1, U3.2
NET_U3_3: R17.1, U3.3
NET_U3_7: R14.1, U3.7
NET_U6_3: R19.1, U6.3
NET_U6_5: R18.1, U6.5
NET_U6_7: R20.2, R21.1, U6.7
NET_U7_1: R23.1, R24.1, U7.1
NET_U7_3: R25.2, R26.1, U7.3
NET_U7_4: R22.1, U7.4, U10.4, U11.2
NET_U8_1: R2.1, U8.1, U8.2
PROC_SYS_JTCK_SWCLK: R11.1, U1.37, U2.9
PROC_SYS_JTDI: R9.1, U1.38, U2.5
PROC_SYS_JTDO_TRACESWO: U1.39, U2.13
PROC_SYS_JTMS_SWDIO: R10.1, U1.34, U2.7
PROC_SYS_JTRST: R8.1, U1.40, U2.3
RST_OUT_U2_SRESET_B: R12.1, U2.15, U10.1
VCC_S1_16V3: C16.1, C19.1, C20.1, J1.1, R19.2, U6.8
VCC_TIER1_3V3: C1.1, C2.1, C3.1, C4.1, C5.1, C13.1, C14.1, C15.1, C17.1, C18.1, C21.1, C22.1, F1.2, R1.2, R3.2, R4.2, R5.2, R6.2, R8.2, R9.2, R10.2, R11.2, R12.2, R15.2, R18.2, R20.1, R22.2, R23.2, R25.1, U1.24, U1.36, U1.48, U2.1, U2.2, U3.8, U6.1, U7.6, U10.5, U11.5
